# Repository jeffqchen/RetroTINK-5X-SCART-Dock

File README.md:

# RetroTINK 5X SCART Dock

Mike Chi's [RetroTINK 5X Pro](https://www.retrotink.com/product-page/5x-pro) is a blessing to the entire retro-gaming community. However the SCART port on the 5X has its issue, not to mention that nobody has any love left for the SCART standard itself. Personally, I'm also a fan of vertical stands for my devices. So here's my approach to tackle the matters.

This dock system puts the RetroTINK 5X into a vertical standing position. It taps into the SCART port, so RGBS + audio signals could be fed into the 5X, while providing extra stability.

------------

There are two version of the dock. One that uses the standard BNC and 3.5mm audio headers, and the other that makes use of my [VGA RGBS + audio pinout standard](https://github.com/jeffqchen/Console-VGA-Dongle-Series).

## [Building The VGA Dock](https://github.com/jeffqchen/RetroTINK-5X-SCART-Dock/tree/main/VGA_Dock)

&nbsp;

-----------

## [Building The BNC Dock](https://github.com/jeffqchen/RetroTINK-5X-SCART-Dock/tree/main/BNC_Dock)

&nbsp;

------------

## Misc

If you are bothered by the single LED inside the RetroTINK 5X, here is a 3D-printed light diffuser that fixes it.

https://www.thingiverse.com/thing:4981210

------------

## Special Thanks

Mike Chi, creator of the RetroTINK 5X. Helped me in various aspects of this project as well.
- Website: https://www.retrotink.com
- Twitter: https://twitter.com/retrotink2

------------

Shield: [![CC BY-SA 4.0][cc-by-sa-shield]][cc-by-sa]

This work is licensed under a
[Creative Commons Attribution-ShareAlike 4.0 International License][cc-by-sa].

[![CC BY-SA 4.0][cc-by-sa-image]][cc-by-sa]

[cc-by-sa]: http://creativecommons.org/licenses/by-sa/4.0/
[cc-by-sa-image]: https://licensebuttons.net/l/by-sa/4.0/88x31.png
[cc-by-sa-shield]: https://img.shields.io/badge/License-CC%20BY--SA%204.0-lightgrey.svg

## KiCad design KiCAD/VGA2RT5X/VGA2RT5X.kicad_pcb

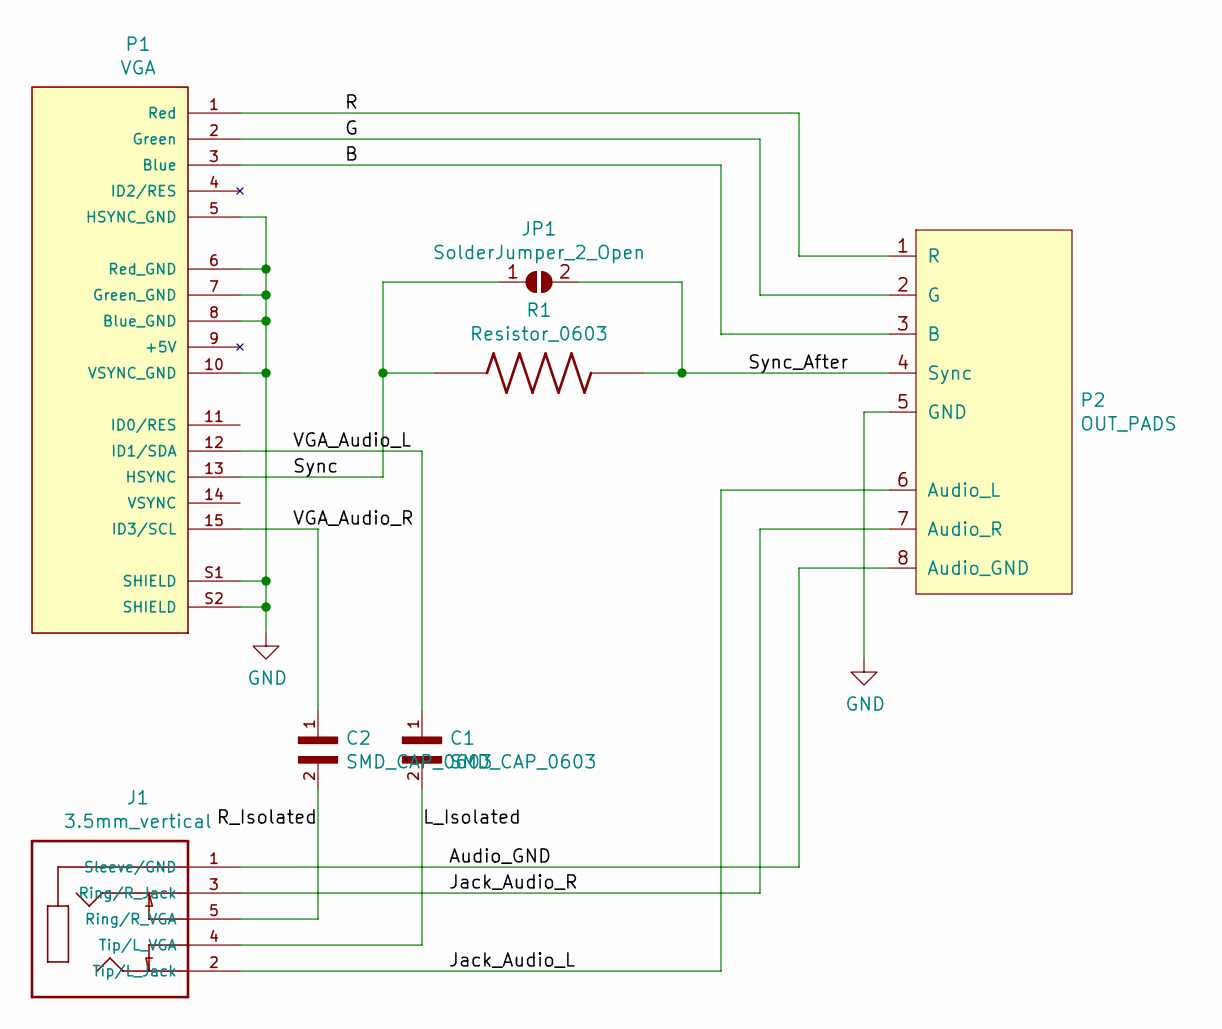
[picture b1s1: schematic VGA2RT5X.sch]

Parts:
C1, C2: SMD_CAP_0603; SMD_Cap_0603
J1: 3.5mm_vertical; 3.5mm_Jack_5p; PARTREV 1.01
JP1: SolderJumper_2_Open; SolderJumper-2_P1.3mm_Open_RoundedPad1.0x1.5mm
P1: VGA; VGA_female_rightangle_slim; PARTREV N/A
P2: OUT_PADS; Output_Pads
R1: Resistor_0603

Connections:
/Audio_GND: J1.1 (Sleeve/GND), P2.8 (Audio_GND)
/B: P1.3 (Blue), P2.3 (B)
/G: P1.2 (Green), P2.2 (G)
/Jack_Audio_L: J1.2 (Tip/L_Jack), P2.6 (Audio_L)
/Jack_Audio_R: J1.3 (Ring/R_Jack), P2.7 (Audio_R)
/L_Isolated: C1.2, J1.4 (Tip/L_VGA)
/R: P1.1 (Red), P2.1 (R)
/R_Isolated: C2.2, J1.5 (Ring/R_VGA)
/Sync: JP1.1 (A), P1.13 (HSYNC), R1.1
/Sync_After: JP1.2 (B), P2.4 (Sync), R1.2
/VGA_Audio_L: C1.1, P1.12 (ID1/SDA)
/VGA_Audio_R: C2.1, P1.15 (ID3/SCL)
GND: P1.5 (HSYNC_GND), P1.6 (Red_GND), P1.7 (Green_GND), P1.8 (Blue_GND), P1.10 (VSYNC_GND), P1.S1 (SHIELD), P1.S2 (SHIELD), P2.5 (GND)

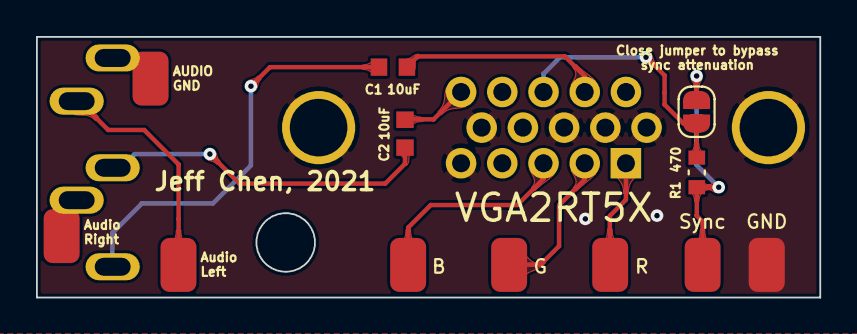
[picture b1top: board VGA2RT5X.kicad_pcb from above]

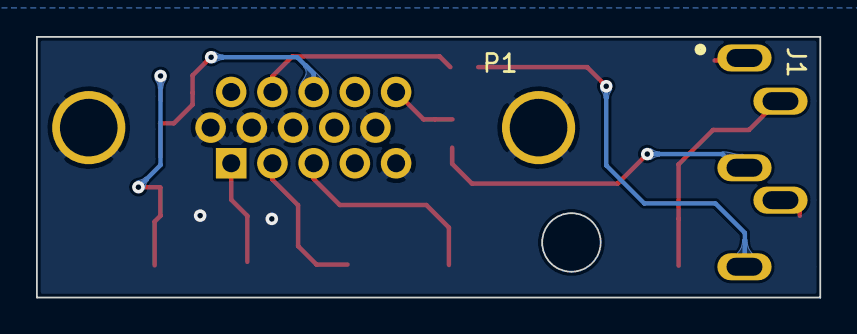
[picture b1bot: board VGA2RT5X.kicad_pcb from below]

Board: 2 copper layers, 43.5 x 14.5 mm, 7 parts (2 on the bottom side), 13 nets.

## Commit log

2021-10-23 Initial Update
2021-10-23 Photos
2021-10-23 Pics and readme
2021-10-23 Updated 3D model for VGA dock
2021-10-23 Update VGA dock readme
2021-11-26 Update readme
    with universal attenuation hack
2022-03-23 Update parts list
2022-08-09 Change license type
